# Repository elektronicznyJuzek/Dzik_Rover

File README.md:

# Dzik_Rover
app_dzik -- window app, controls robot via UDP,
atmega328p_dzik -- PWM generator,
raspberry_dzik -- console app, allows to control robot

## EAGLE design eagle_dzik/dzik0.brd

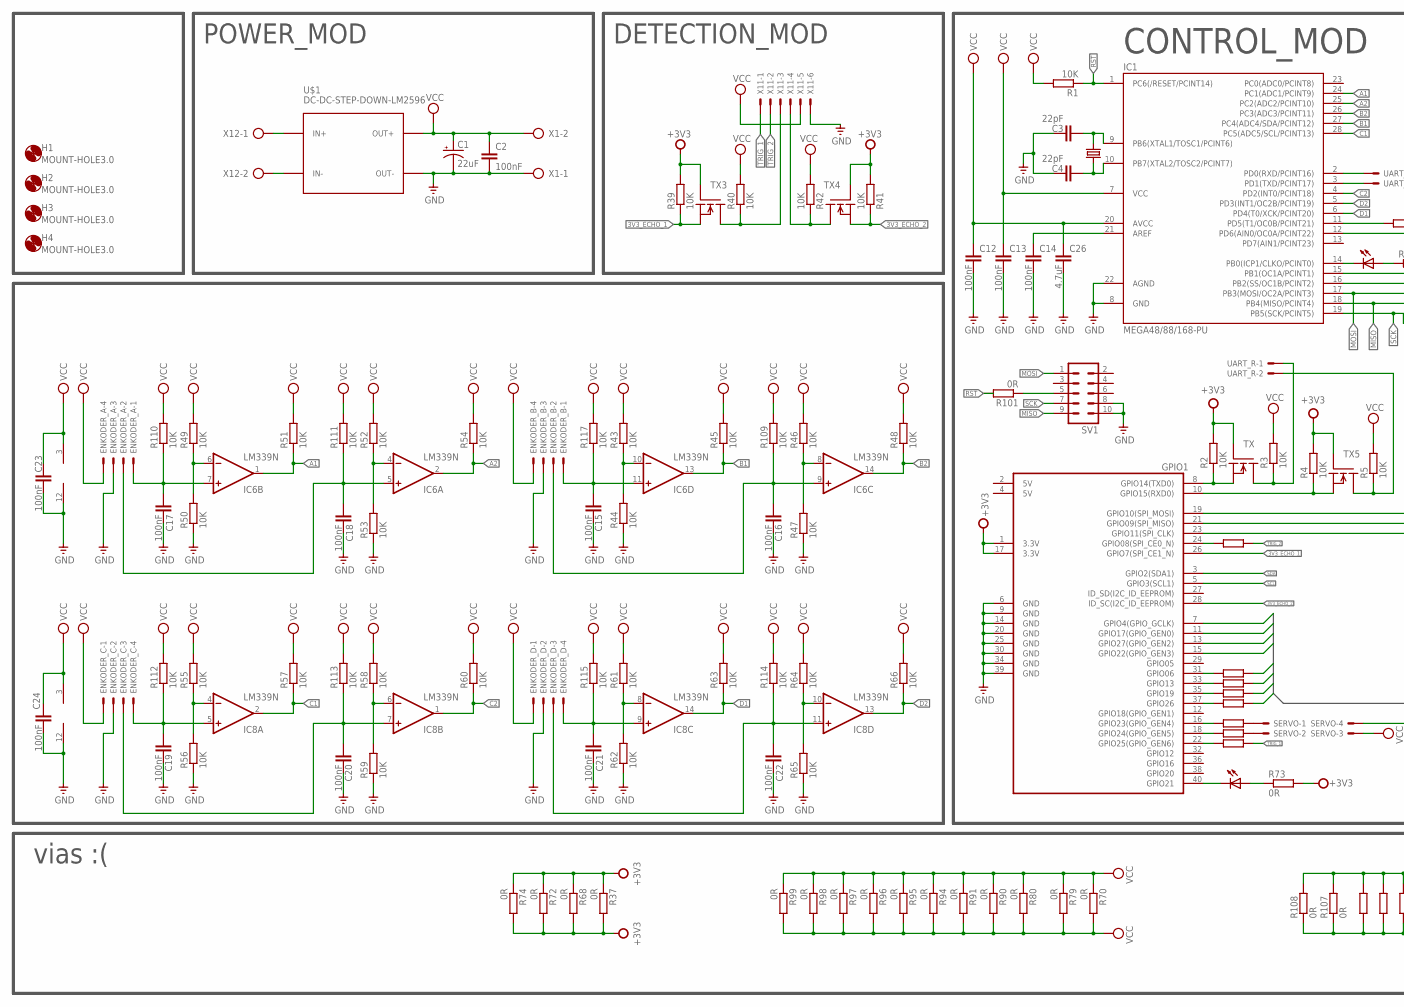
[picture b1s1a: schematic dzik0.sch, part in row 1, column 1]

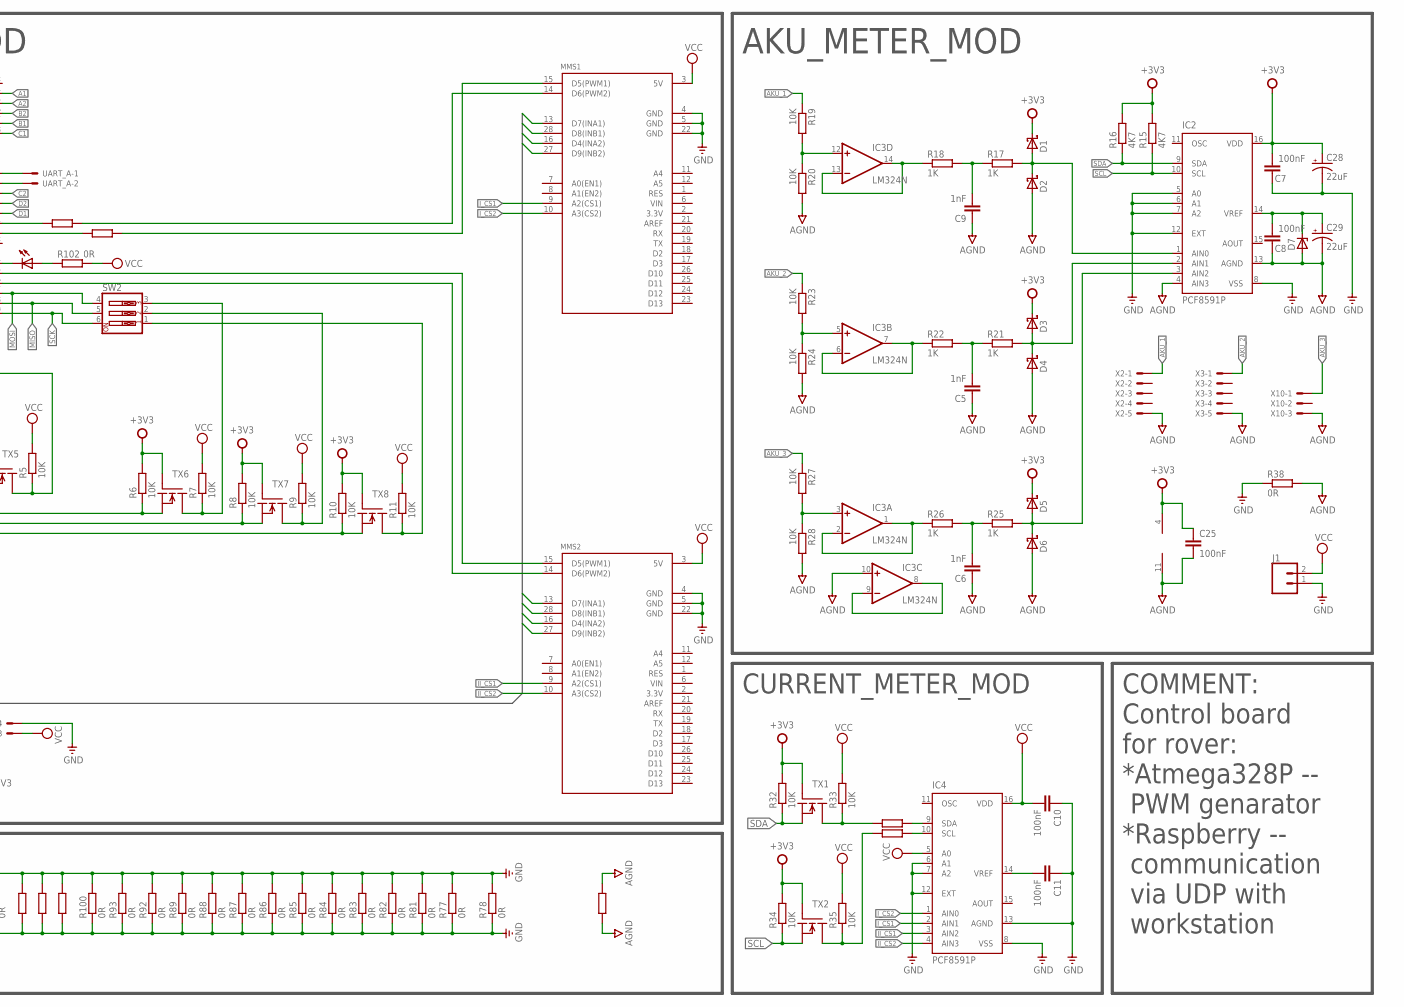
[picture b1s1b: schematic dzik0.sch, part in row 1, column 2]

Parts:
C1, C28, C29: 22uF; E2,5-6
C2, C7, C8, C10, C11, C12, C13, C14, C15, C16, C17, C18, C19, C20, C21, C22, C23, C24, C25: 100nF; C025-024X044
C3, C4: 22pF; C025-024X044
C5, C6, C9: 1nF; C025-024X044
C26: 4.7uF; C050-025X075
D1, D2, D3, D4, D5, D6: SCHOTTKY-DIODEDO35-7; DO35-7
D7: ZENER-DIODEZD-5; ZDIO-5
ENKODER_A: JST-XH-04-PIN-LONG-PAD; JST-XH-04-PACKAGE-LONG-PAD
ENKODER_B: JST-XH-04-PIN-LONG-PAD; JST-XH-04-PACKAGE-LONG-PAD
ENKODER_C: JST-XH-04-PIN-LONG-PAD; JST-XH-04-PACKAGE-LONG-PAD
ENKODER_D: JST-XH-04-PIN-LONG-PAD; JST-XH-04-PACKAGE-LONG-PAD
GPIO1: _GPIO_RASPBERRY; GPIO_RASPBERRY
H1, H2, H3, H4: MOUNT-HOLE3.0; 3,0
IC1: MEGA48/88/168-PU; DIL28-3
IC2, IC4: PCF8591P; DIL16
IC3: LM324N; DIL14
IC6, IC8: LM339N; DIL14
J1: CONN_02; 1X02
LED1, LED3: LED5MM
MMS1, MMS2: MONSTERMOTO_SHIELD; MONSTER_MOTO_1
Q1: 11.520MHz; HC49/S
R1, R2, R3, R4, R5, R6, R7, R8, R9, R10, R11, R19, R20, R23, R24, R27, R28, R32, R33, R34, R35, R39, R40, R41, R42, R43, R44, R45, R46, R47, R48, R49, R50, R51, R52, R53, R54, R55, R56, R57, R58, R59, R60, R61, R62, R63, R64, R65, R66, R109, R110, R111, R112, R113, R114, R115, R117: 10K; 0207/7
R12, R13, R14, R67, R69, R70, R71, R103, R104, R105: 0R; 0207/10
R15, R16: 4K7; 0207/7
R17, R18, R21, R22, R25, R26: 1K; 0207/7
R29, R30, R75, R76: 0R; 0204/7
R31, R36, R37, R38, R68, R72, R73, R74, R77, R78, R79, R80, R81, R82, R83, R84, R85, R86, R87, R88, R89, R90, R91, R92, R93, R94, R95, R96, R97, R98, R99, R100, R101, R102, R106, R107, R108: 0R; 0207/7
SERVO: JST-XH-04-PIN-LONG-PAD; JST-XH-04-PACKAGE-LONG-PAD
SV1: MA05-2
SW2: SW_DIP-3; EDG-03
TX, TX1, TX2, TX3, TX4, TX5, TX6, TX7, TX8: FQN1N50CI; TO92-INLINE
U$1: DC-DC-STEP-DOWN-LM2596
UART_A: JST-XH-02-PIN-LONG-PAD; JST-XH-02-PACKAGE-LONG-PAD
UART_R: JST-XH-02-PIN-LONG-PAD; JST-XH-02-PACKAGE-LONG-PAD
X1, X12: AK300/2
X2, X3: JST-XH-05-PIN-LONG-PAD; JST-XH-05-PACKAGE-LONG-PAD
X10: JST-XH-03-PIN-LONG-PAD; JST-XH-03-PACKAGE-LONG-PAD
X11: JST-XH-06-PIN-LONG-PAD; JST-XH-06-PACKAGE-LONG-PAD

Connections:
3V3_ECHO_1: GPIO1.26 (GPIO7(SPI_CE1_N)), R39.1, TX3.3 (S)
3V3_ECHO_2: GPIO1.28 (ID_SC(I2C_ID_EEPROM)), R41.1, TX4.3 (S)
3V3_MISO: GPIO1.21 (GPIO09(SPI_MISO)), R8.1, TX7.3 (S)
3V3_MOSI: GPIO1.19 (GPIO10(SPI_MOSI)), R6.1, TX6.3 (S)
3V3_SCK: GPIO1.23 (GPIO11(SPI_CLK)), R10.1, TX8.3 (S)
5V_MISO: R9.1, SW2.2, TX7.1 (D)
5V_MOSI: R7.1, SW2.3, TX6.1 (D)
5V_SCK: R11.1, SW2.1, TX8.1 (D)
+3V3: C7.2, C25.1, C28.+, D1.C, D3.C, D5.C, GPIO1.1 (3.3V), GPIO1.17 (3.3V), IC2.16 (VDD), IC3.4 (V+), R2.2, R4.2, R6.2, R8.2, R10.2, R15.2, R16.2, R32.2, R34.2, R37.1, R37.2, R39.2, R41.2, R68.1, R68.2, R72.1, R72.2, R73.2, R74.1, R74.2, TX.2 (G), TX1.2 (G), TX2.2 (G), TX3.2 (G), TX4.2 (G), TX5.2 (G), TX6.2 (G), TX7.2 (G), TX8.2 (G)
A1: IC1.24 (PC1(ADC1/PCINT9)), IC6.1 (OUT), R51.1
A2: IC1.25 (PC2(ADC2/PCINT10)), IC6.2 (OUT), R54.1
AGND: C5.1, C6.1, C8.1, C9.1, C25.2, C29.-, D2.A, D4.A, D6.A, D7.A, IC2.4 (AIN3), IC2.13 (AGND), IC3.10 (+IN), IC3.11 (V-), R20.2, R24.2, R28.2, R38.2, R106.1, R106.2, X2.5, X3.5, X10.3
AKU_1: R19.1, X2.1
AKU_2: R23.1, X3.1
AKU_3: R27.1, X10.1
B1: IC1.27 (PC4(ADC4/SDA/PCINT12)), IC6.13 (OUT), R45.1
B2: IC1.26 (PC3(ADC3/PCINT11)), IC6.14 (OUT), R48.1
C1: IC1.28 (PC5(ADC5/SCL/PCINT13)), IC8.2 (OUT), R57.1
C2: IC1.4 (PD2(INT0/PCINT18)), IC8.1 (OUT), R60.1
D1: IC1.6 (PD4(T0/XCK/PCINT20)), IC8.14 (OUT), R63.1
D2: IC1.5 (PD3(INT1/OC2B/PCINT19)), IC8.13 (OUT), R66.1
E1_0: GPIO1.31 (GPIO06), R14.1
E1_1: GPIO1.33 (GPIO13), R67.1
E1_2: GPIO1.35 (GPIO19), R69.1
E1_3: GPIO1.37 (GPIO26), R71.1
ECHO_1: R40.1, TX3.1 (D), X11.3
ECHO_2: R42.1, TX4.1 (D), X11.4
GND: C1.-, C2.2, C3.1, C4.1, C7.1, C10.1, C11.1, C12.2, C13.2, C14.2, C15.2, C16.2, C17.2, C18.2, C19.2, C20.2, C21.2, C22.2, C23.2, C24.2, C26.2, C28.-, ENKODER_A.3, ENKODER_B.3, ENKODER_C.2, ENKODER_D.2, GPIO1.6 (GND), GPIO1.9 (GND), GPIO1.14 (GND), GPIO1.20 (GND), GPIO1.25 (GND), GPIO1.30 (GND), GPIO1.34 (GND), GPIO1.39 (GND), IC1.8 (GND), IC1.22 (AGND), IC2.5 (A0), IC2.6 (A1), IC2.7 (A2), IC2.8 (VSS), IC2.12 (EXT), IC4.6 (A1), IC4.7 (A2), IC4.8 (VSS), IC4.12 (EXT), IC4.13 (AGND), IC6.12 (GND), IC8.12 (GND), J1.1, MMS1.4 (GND), MMS1.5 (GND), MMS1.22 (GND), MMS2.4 (GND), MMS2.5 (GND), MMS2.22 (GND), R38.1, R44.1, R47.1, R50.1, R53.1, R56.1, R59.1, R62.1, R65.1, R77.1, R77.2, R78.1, R78.2, R81.1, R81.2, R82.1, R82.2, R83.1, R83.2, R84.1, R84.2, R85.1, R85.2, R86.1, R86.2, R87.1, R87.2, R88.1, R88.2, R89.1, R89.2, R92.1, R92.2, R93.1, R93.2, R100.1, R100.2, R103.1, R103.2, R104.1, R104.2, R105.1, R105.2, R107.1, R107.2, R108.1, R108.2, SERVO.4, SV1.8, SV1.10, U$1.OUT-, X1.1, X11.6
II_CS1: IC4.3 (AIN2), MMS2.9 (A2(CS1))
II_CS2: IC4.4 (AIN3), MMS2.10 (A3(CS2))
II_D4: GPIO1.15 (GPIO22(GPIO_GEN3)), MMS2.16 (D4(INA2))
II_D7: GPIO1.13 (GPIO27(GPIO_GEN2)), MMS2.13 (D7(INA1))
II_D8: GPIO1.11 (GPIO17(GPIO_GEN0)), MMS2.28 (D8(INB1))
II_D9: GPIO1.7 (GPIO4(GPIO_GCLK)), MMS2.27 (D9(INB2))
I_CS1: IC4.2 (AIN1), MMS1.9 (A2(CS1))
I_CS2: IC4.1 (AIN0), MMS1.10 (A3(CS2))
I_D4: MMS1.16 (D4(INA2)), R14.2
I_D7: MMS1.13 (D7(INA1)), R67.2
I_D8: MMS1.28 (D8(INB1)), R69.2
I_D9: MMS1.27 (D9(INB2)), R71.2
MISO: IC1.18 (PB4(MISO/PCINT4)), SV1.9, SW2.5
MOSI: IC1.17 (PB3(MOSI/OC2A/PCINT3)), SV1.1, SW2.4
MOSI1: R33.1, R36.1, TX1.1 (D)
MOSI2: R5.1, TX5.1 (D), UART_R.2
MOSI3: R3.1, TX.1 (D), UART_R.1
MOSI4: R31.1, R35.1, TX2.1 (D)
unnamed: C15.1, ENKODER_B.1, IC6.11 (+IN), R117.1
unnamed: C4.2, IC1.10 (PB7(XTAL2/TOSC2/PCINT7)), Q1.1
unnamed: MMS1.15 (D5(PWM1)), R13.2
unnamed: MMS1.14 (D6(PWM2)), R12.2
unnamed: GPIO1.24 (GPIO08(SPI_CE0_N)), R29.1
unnamed: GPIO1.22 (GPIO25(GPIO_GEN6)), R30.1
unnamed: C16.1, ENKODER_B.2, IC6.9 (+IN), R109.1
unnamed: IC6.10 (-IN), R43.1, R44.2
unnamed: IC4.9 (SDA), R36.2
unnamed: IC6.8 (-IN), R46.1, R47.2
unnamed: IC3.8 (OUT), IC3.9 (-IN)
unnamed: C17.1, ENKODER_A.1, IC6.7 (+IN), R110.1
unnamed: C19.1, ENKODER_C.4, IC8.5 (+IN), R112.1
unnamed: IC8.4 (-IN), R55.1, R56.2
unnamed: GPIO1.10 (GPIO15(RXD0)), R4.1, TX5.3 (S)
unnamed: GPIO1.8 (GPIO14(TXD0)), R2.1, TX.3 (S)
unnamed: C8.2, C29.+, D7.C, IC2.14 (VREF)
unnamed: C14.1, IC1.21 (AREF)
unnamed: GPIO1.40 (GPIO21), LED3.K (C)
unnamed: IC4.10 (SCL), R31.2
unnamed: U$1.IN+, X12.1
unnamed: IC1.3 (PD1(TXD/PCINT17)), UART_A.2
unnamed: U$1.IN-, X12.2
unnamed: IC6.6 (-IN), R49.1, R50.2
unnamed: IC6.4 (-IN), R52.1, R53.2
unnamed: GPIO1.18 (GPIO24(GPIO_GEN5)), R75.1
unnamed: C18.1, ENKODER_A.2, IC6.5 (+IN), R111.1
unnamed: GPIO1.16 (GPIO23(GPIO_GEN4)), R76.1
unnamed: IC1.2 (PD0(RXD/PCINT16)), UART_A.1
unnamed: IC8.6 (-IN), R58.1, R59.2
unnamed: IC3.5 (+IN), R23.2, R24.1
unnamed: R75.2, SERVO.2
unnamed: IC3.3 (+IN), R27.2, R28.1
unnamed: IC3.12 (+IN), R19.2, R20.1
unnamed: C3.2, IC1.9 (PB6(XTAL1/TOSC1/PCINT6)), Q1.2
unnamed: R76.2, SERVO.1
unnamed: LED1.A, R102.1
unnamed: IC1.14 (PB0(ICP1/CLKO/PCINT0)), LED1.K (C)
unnamed: R101.1, SV1.5
unnamed: D1.A, D2.C, IC2.1 (AIN0), R17.2
unnamed: C9.2, R17.1, R18.2
unnamed: D3.A, D4.C, IC2.2 (AIN1), R21.2
unnamed: D5.A, D6.C, IC2.3 (AIN2), R25.2
unnamed: C5.2, R21.1, R22.2
unnamed: C11.2, IC4.14 (VREF)
unnamed: C6.2, R25.1, R26.2
unnamed: LED3.A, R73.1
unnamed: IC3.13 (-IN), IC3.14 (OUT), R18.1
unnamed: C20.1, ENKODER_C.3, IC8.7 (+IN), R113.1
unnamed: IC3.6 (-IN), IC3.7 (OUT), R22.1
unnamed: C21.1, ENKODER_D.4, IC8.9 (+IN), R115.1
unnamed: IC8.8 (-IN), R61.1, R62.2
unnamed: IC8.10 (-IN), R64.1, R65.2
unnamed: IC3.1 (OUT), IC3.2 (-IN), R26.1
unnamed: C22.1, ENKODER_D.3, IC8.11 (+IN), R114.1
PWM1: IC1.12 (PD6(AIN0/OC0A/PCINT22)), R13.1
PWM2: IC1.11 (PD5(T1/OC0B/PCINT21)), R12.1
PWM3: IC1.15 (PB1(OC1A/PCINT1)), MMS2.15 (D5(PWM1))
PWM4: IC1.16 (PB2(SS/OC1B/PCINT2)), MMS2.14 (D6(PWM2))
RST: IC1.1 (PC6(/RESET/PCINT14)), R1.1, R101.2
SCK: IC1.19 (PB5(SCK/PCINT5)), SV1.7, SW2.6
SCL: GPIO1.5 (GPIO3(SCL1)), IC2.10 (SCL), R15.1, R34.1, TX2.3 (S)
SDA: GPIO1.3 (GPIO2(SDA1)), IC2.9 (SDA), R16.1, R32.1, TX1.3 (S)
TRIG_1: R30.2, X11.1
TRIG_2: R29.2, X11.2
VCC: C1.+, C2.1, C10.2, C12.1, C13.1, C23.1, C24.1, C26.1, ENKODER_A.4, ENKODER_B.4, ENKODER_C.1, ENKODER_D.1, IC1.7 (VCC), IC1.20 (AVCC), IC4.5 (A0), IC4.16 (VDD), IC6.3 (V+), IC8.3 (V+), J1.2, MMS1.3 (5V), MMS2.3 (5V), R1.2, R3.2, R5.2, R7.2, R9.2, R11.2, R33.2, R35.2, R40.2, R42.2, R43.2, R45.2, R46.2, R48.2, R49.2, R51.2, R52.2, R54.2, R55.2, R57.2, R58.2, R60.2, R61.2, R63.2, R64.2, R66.2, R70.1, R70.2, R79.1, R79.2, R80.1, R80.2, R90.1, R90.2, R91.1, R91.2, R94.1, R94.2, R95.1, R95.2, R96.1, R96.2, R97.1, R97.2, R98.1, R98.2, R99.1, R99.2, R102.2, R109.2, R110.2, R111.2, R112.2, R113.2, R114.2, R115.2, R117.2, SERVO.3, U$1.OUT+, X1.2, X11.5

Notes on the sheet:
CONTROL_MOD
DETECTION_MOD
AKU_METER_MOD
CURRENT_METER_MOD
COMMENT:
vias :(
POWER_MOD
Control board for rover: *Atmega328P -- PWM genarator *Raspberry -- communication via UDP with workstation

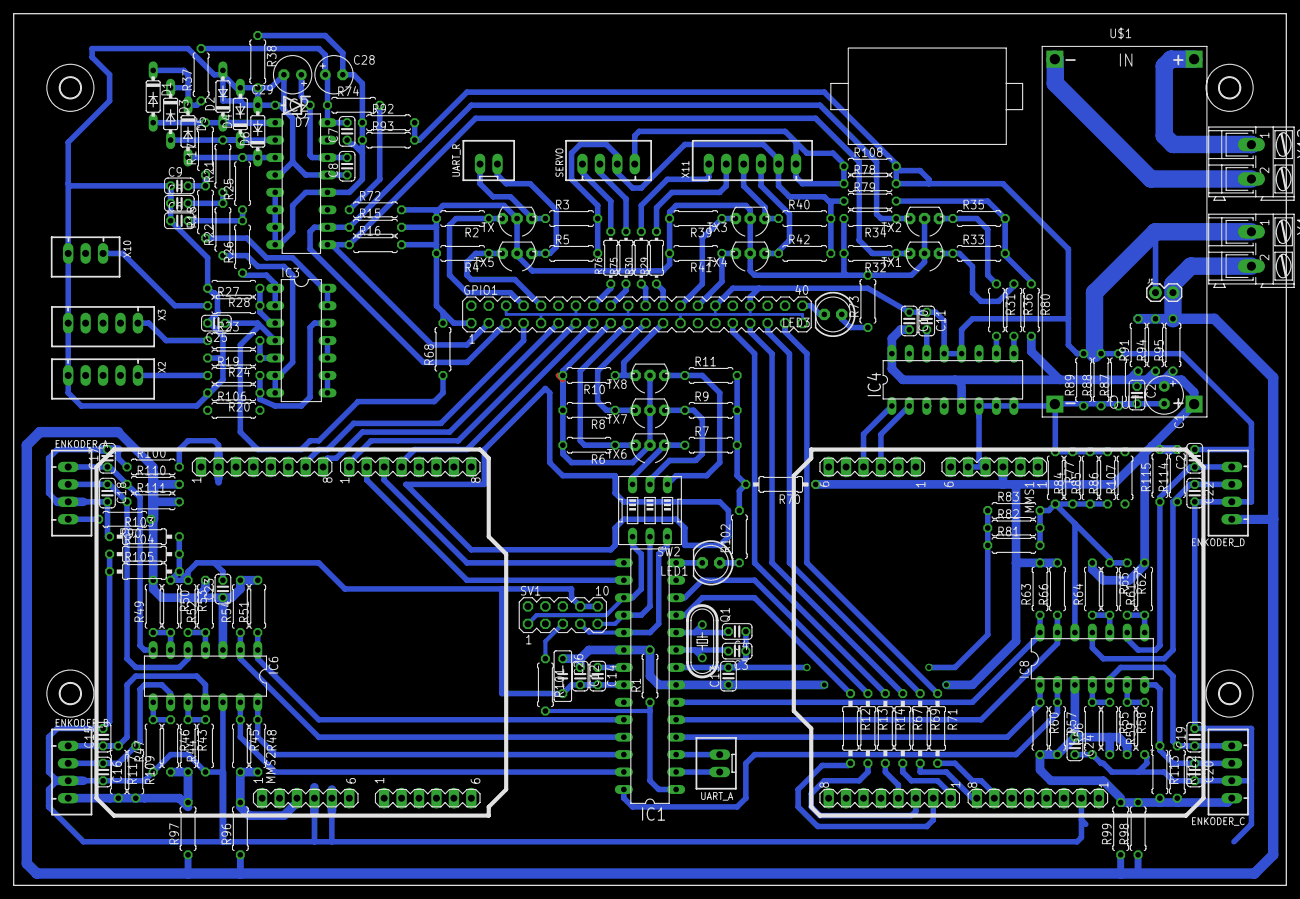
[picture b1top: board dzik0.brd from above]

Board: 2 copper layers, 185.4 x 127.0 mm, 194 parts (0 on the bottom side), 112 nets.

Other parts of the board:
U$2: VOLTOMIERZ

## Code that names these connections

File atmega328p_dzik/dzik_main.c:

/*
 * dzik_main.c
 *
 *  Created on: 26 lis 2017
 *      Author: Juzek
 */
#include <avr/io.h>

/*****************\
*                 *
*  ###        ### *
*  #1#=@@@@@@=#3# *
*  ### @@@@@@ ### *
*      @@@@@@     *
*  ### @@@@@@ ### *
*  #2#=@@@@@@=#4# *
*  ###        ### *
*                 *
\*****************/

int main(void)
{
	DDRD |= (1<<PD5)|(1<<PD6)|(1<<PD3);
	DDRB |= (1<<PB1);

	// TIMER0 -- FAST PWM
	TCCR0A |= (1<<WGM01)|(1<<WGM00);	// -- fast PWM
	TCCR0A |= (1<<COM0A1)|(1<<COM0B1);	// -- non-inverting mode
	TCCR0B |= (1<<CS01);				// -- prescaler == 8

	// TIMER1 -- FAST PWM
	TCCR1A |= (1<<WGM10);				// -- fast PWM
	TCCR1B |= (1<<WGM12);				// -- fast PWM
	TCCR1A |= (1<<COM1A1);				// -- non-invertng mode
	TCCR1B |= (1<<CS11);				// -- prescaler == 8

	// TIMER2 -- FAST PWM
	TCCR2A |= (1<<WGM20)|(1<<WGM21);	// -- fast PWM
	TCCR2A |= (1<<COM2B1);				// -- non-inverting mode
	TCCR2B |= (1<<CS21);				// prescaler == 8

	OCR0A = 100;
	OCR0B = 100;
	OCR1A = 100;
	OCR2B = 100;

	while(1);
}

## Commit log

2017-11-22 test
2017-11-22 no message
2017-11-27 First version of the soft

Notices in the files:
parts and their libraries:
diy-modules: Released under the Creative Commons Attribution 4.0 International License: http://creativecommons.org/licenses/by/4.0
sparkfun_connectors: Licensing: Creative Commons ShareAlike 4.0 International - https://creativecommons.org/licenses/by-sa/4.0
